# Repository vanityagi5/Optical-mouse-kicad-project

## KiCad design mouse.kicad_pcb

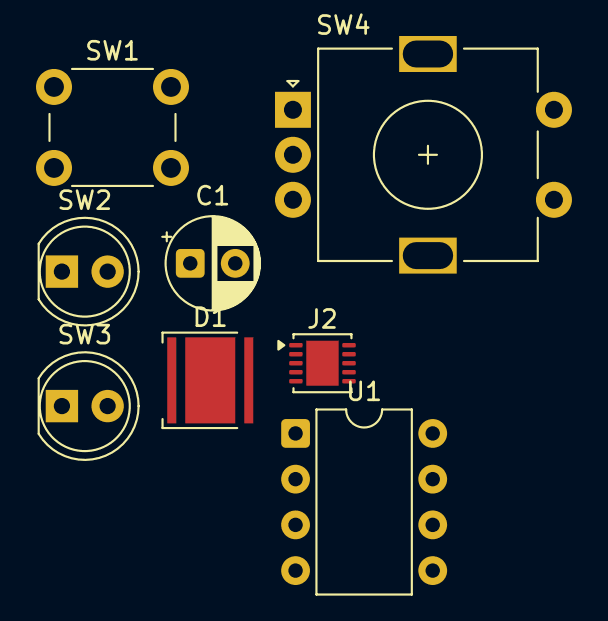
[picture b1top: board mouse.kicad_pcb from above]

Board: 2 copper layers, 8 parts (0 on the bottom side), 7 nets, no tracks yet.

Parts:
C1: C_Polarized; CP_Radial_D5.0mm_P2.50mm
D1: LED; LED_Cree-XHP50_3V_HighDensity
J2: Conn_01x05_Socket; WDFN-10-1EP_3x3mm_P0.5mm_EP1.8x2.5mm
SW1: SW_Push; SW_PUSH_6mm
SW2, SW3: SW_Push; LED_D5.0mm
SW4: RotaryEncoder; RotaryEncoder_Alps_EC11E-Switch_Vertical_H20mm
U1: ADNS_5020; DIP-8_W7.62mm

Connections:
GND: C1.2, D1.1 (K), SW1.2 (2_2), SW2.2 (2_2), SW3.2 (2_2), SW4.C, U1.8
unnamed: D1.2 (A), U1.7
unnamed: C1.1, J2.1, U1.1
unnamed: J2.2, U1.2
unnamed: J2.3, SW4.A, U1.3
unnamed: J2.4, SW4.B, U1.4
unnamed: J2.5, U1.5
